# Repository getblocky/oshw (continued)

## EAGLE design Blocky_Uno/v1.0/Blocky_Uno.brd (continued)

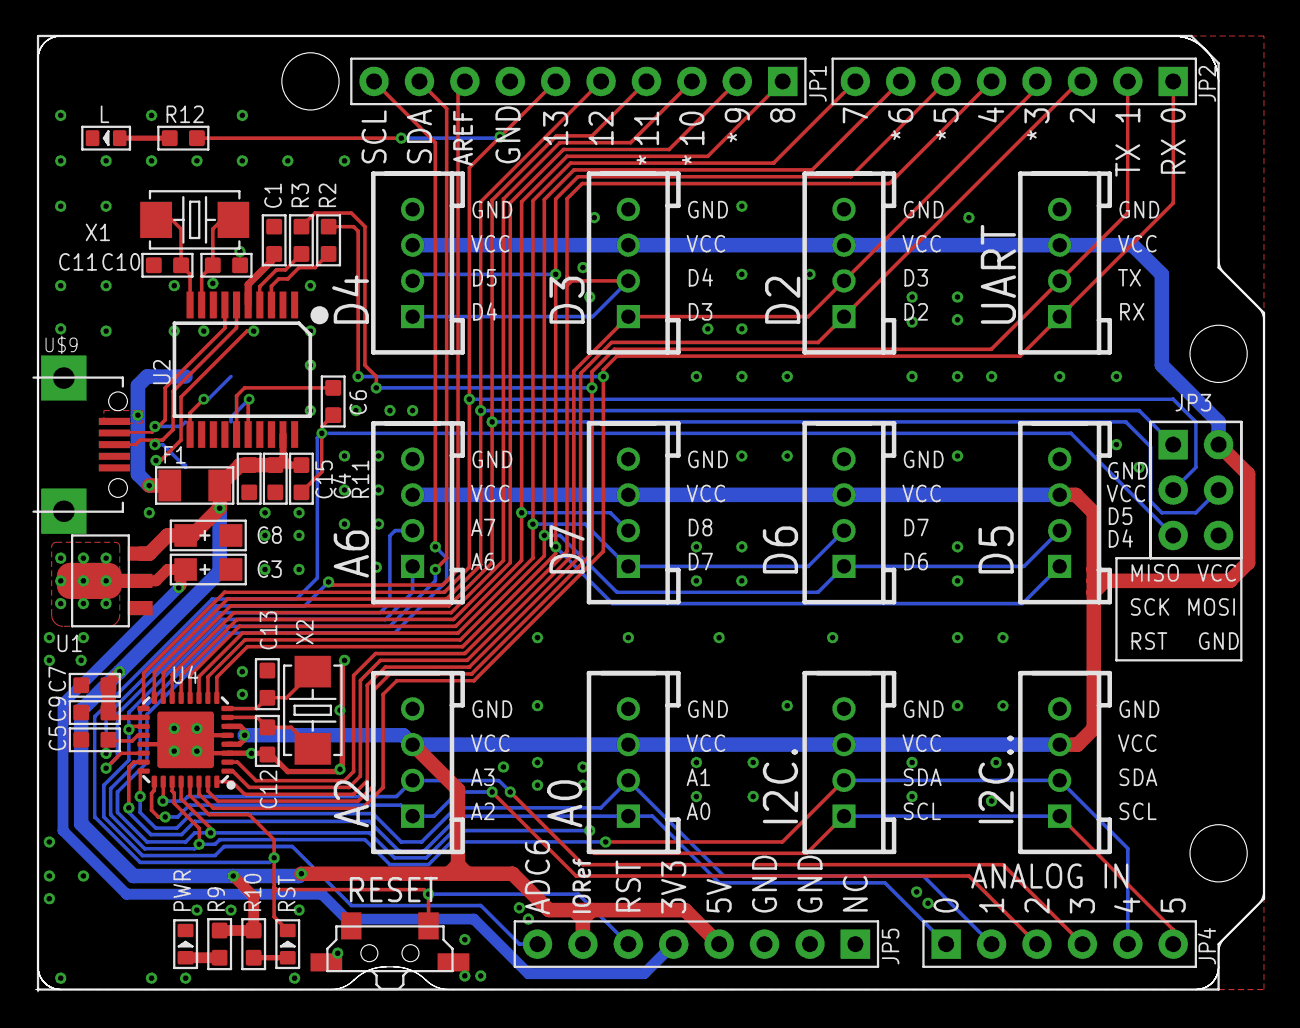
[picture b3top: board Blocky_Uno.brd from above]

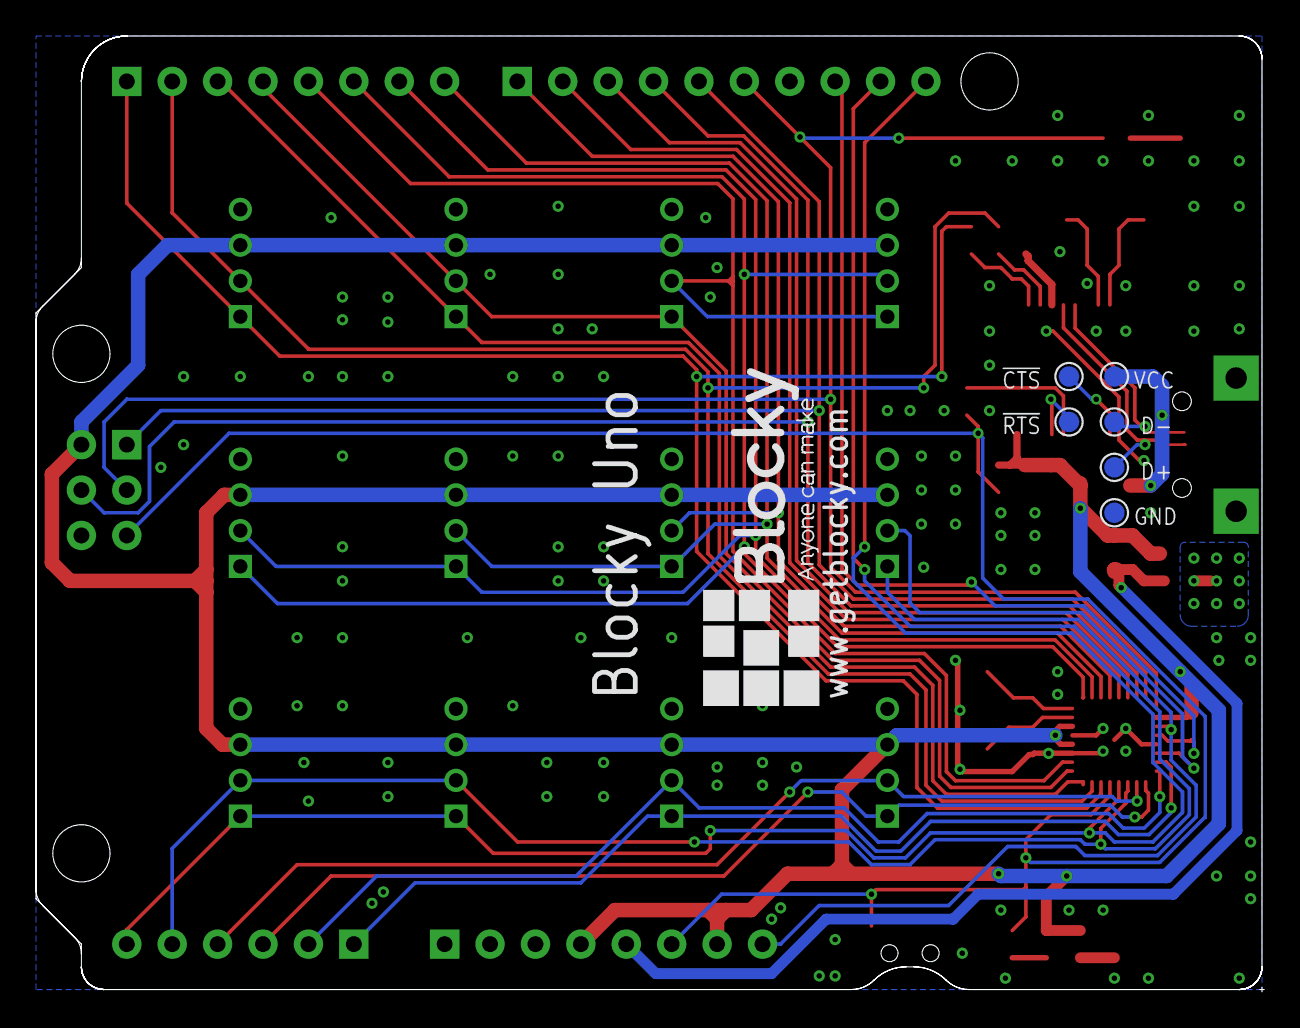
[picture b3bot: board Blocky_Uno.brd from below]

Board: 2 copper layers, 68.7 x 53.5 mm, 51 parts (7 on the bottom side), 43 nets.

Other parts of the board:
U$4: BLOCKY_LOGO
U$12: SEEED_MASK

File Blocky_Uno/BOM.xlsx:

| Part | Package | Quantity | Link
 | DIP Grove | 4P-2.0 | 12
 | 10nF | C0603 | 1
 | Cap tantalum 3216 22uF 10V | AVX-A 3216 | 2 | https://www.aliexpress.com/item/Free-shipping-20pcs-A-3216-2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
 | 100nF | C0603 | 6
 | 12pF | C0603 | 4
 | Fuse 1206 500mA | F1206 | 1 | https://www.aliexpress.com/item/100PCS-1206-0-5A-0-5-Amp-500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
 | MICRO-B-SMD 10118193-0001LF | MICRO-USB | 1 | https://www.digikey.com/product-detail/en/amphenol-fci/10118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
 | LED GREEN | LED-0603 | 2
 | Resistor 1k | R0603 | 5
 | Resistor 10k | R0603 | 1
 | Side SMD Tact Switch 3.5x7.0x3.5 TS-118E | 4P-SMD-7X3.5X3.5H | 1 | https://www.aliexpress.com/item/1000pcs-on-tape-reel-Horizon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
 | LED RED | LED-0603 | 1
 | LDO AMS1117-3.3V SOT89 | SOT89 | 1 | https://www.aliexpress.com/item/100PCS-AMS1117-3-3V-AMS1117-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
 | CH340T | SSOP20 | 1 | https://www.aliexpress.com/item/Smd-CH340T-wch-usb-to-serial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
 | Atmega328p-mu | MLF32X-W/HEAT | 1 | https://www.aliexpress.com/item/Free-Shipping-ATMEGA328P-MUR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
 | Crystal SMD 5032 12MHz | 2P-SMD-5X3.2 | 1 | https://www.aliexpress.com/item/NDK-NX5032GA-NX5032GB-12M-12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
 | Crystal SMD 5032 16MHz | 2P-SMD-5X3.2 | 1 | Crystal SMD 16MHz 5032 https://www.aliexpress.com/item/20PCS-16MHZ-5032-SMD-Pas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

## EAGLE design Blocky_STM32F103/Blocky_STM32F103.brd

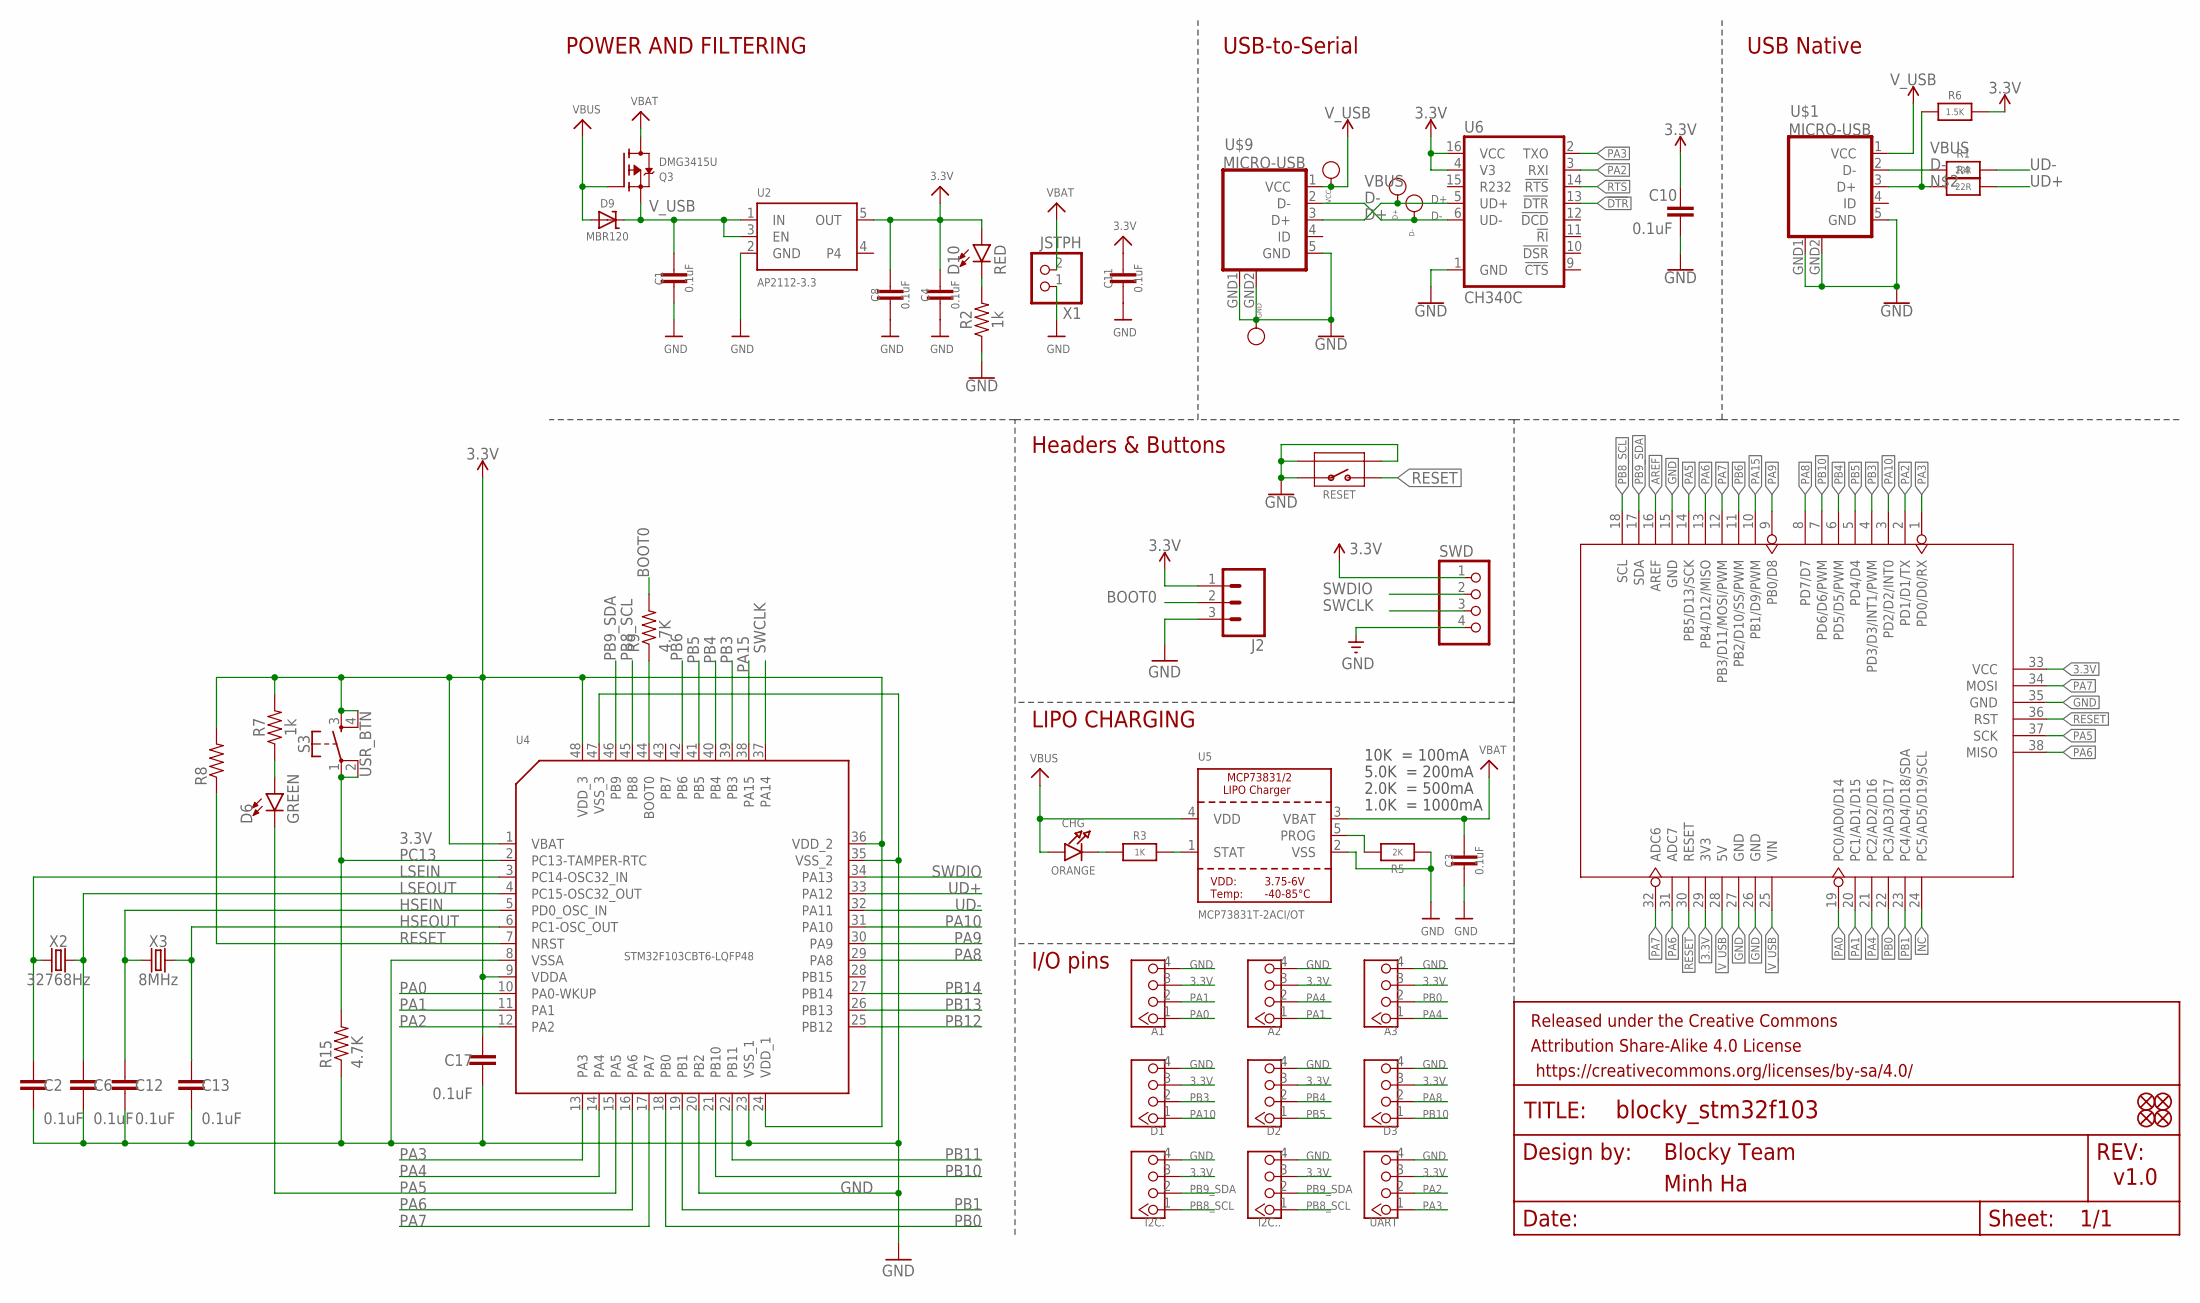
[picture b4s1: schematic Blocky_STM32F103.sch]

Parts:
A1, A2, A3: TWIG-4P-2.0-2.0; 4P-2.0
C1, C2, C3, C4, C6, C8, C10, C11, C12, C13, C17: 0.1uF; 0603
CHG: ORANGE; CHIPLED_0603
D1, D2, D3: TWIG-4P-2.0-2.0; 4P-2.0
D6: GREEN; LED-0603
D9: MBR120; SOD-123
D10: RED; LED-0603
D+: PAD-TEST-POINT'4545'; TP_4545
D-: PAD-TEST-POINT'4545'; TP_4545
FD1, FD2, FD3, FD4: FIDUCIAL1X2; FIDUCIAL-1X2
FRAME1: FRAME-LETTERNO_PACKAGE; DUMMY
GND: PAD-TEST-POINT'4545'; TP_4545
I2C., I2C..: TWIG-4P-2.0-2.0; 4P-2.0
J2: CONN_031X03_NO_SILK; 1X03_NO_SILK
Q3: DMG3415U; SOT23-R
R1, R4: 22R; 0603-NO
R2, R7: 1k; 0603
R3: 1K; 0603-NO
R5: 2K; 0603-NO
R6: 1.5K; 0603-NO
R8: 0603
R9, R15: 4.7K; 0603
RESET: BUTTON-4P-REINFORCE'TS-1188E'; 4P-SMD-7X3.5X3.5H
S3: USR_BTN; TACTILE_SWITCH_SMD_4.6X2.8MM
SWD: HEADER-1X4ROUND; 1X04_ROUND
U2: AP2112-3.3; SOT23-5
U3: ARDUINO-38P
U4: STM32F103CBT6-LQFP48; LQFP48-0.5-7X7MM
U5: MCP73831T-2ACI/OT; SOT23-5
U6: CH340C; SO016
U$1, U$9: MICRO-USB
UART: TWIG-4P-2.0-2.0; 4P-2.0
VCC: PAD-TEST-POINT'4545'; TP_4545
X1: JSTPH; JSTPH2
X2: 32768Hz; CRYSTAL-SMD-3.2X1.5MM
X3: 8MHz; CRYSTAL-SMD-5X3.2-2PAD

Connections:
3.3V: A1.3, A2.3, A3.3, C4.1, C8.1, C10.1, C11.1, C17.1, D1.3, D2.3, D3.3, D10.A, I2C..3, I2C...3, J2.1, R6.2, R7.2, R8.2, S3.3, S3.4, SWD.1, U2.5 (OUT), U3.29 (3V3), U3.33 (VCC), U4.1 (VBAT), U4.9 (VDDA), U4.24 (VDD_1), U4.36 (VDD_2), U4.48 (VDD_3), U6.4 (V3), U6.16 (VCC), UART.3
!DTR: U6.13 (!DTR)
!RTS: U6.14 (!RTS)
AREF: U3.16 (AREF)
BOOT0: J2.2, R9.2
D+: D+.T, U6.5 (UD+), U$9.3 (D+)
D-: D-.T, R1.1, U6.6 (UD-), U$1.2 (D-), U$9.2 (D-)
GND: A1.4, A2.4, A3.4, C1.2, C2.2, C3.2, C4.2, C6.2, C8.2, C10.2, C11.2, C12.2, C13.2, C17.2, D1.4, D2.4, D3.4, GND.T, I2C..4, I2C...4, J2.3, R2.1, R5.1, R15.1, RESET.1, RESET.S1, RESET.S2, SWD.4, U2.2 (GND), U3.15 (GND), U3.26 (GND), U3.27 (GND), U3.35 (GND), U4.8 (VSSA), U4.20 (PB2), U4.23 (VSS_1), U4.35 (VSS_2), U4.47 (VSS_3), U5.2 (VSS), U6.1 (GND), U$1.5 (GND), U$1.GND1 (GND), U$1.GND2 (GND), U$9.5 (GND), U$9.GND1 (GND), U$9.GND2 (GND), UART.4, X1.1
HSEIN: C12.1, U4.5 (PD0_OSC_IN), X3.P$1 (1)
HSEOUT: C13.1, U4.6 (PC1-OSC_OUT), X3.P$2 (2)
LSEIN: C2.1, U4.3 (PC14-OSC32_IN), X2.P$1 (1)
LSEOUT: C6.1, U4.4 (PC15-OSC32_OUT), X2.P$2 (2)
unnamed: CHG.C, R3.1
unnamed: R4.1, R6.1, U$1.3 (D+)
unnamed: R9.1, U4.44 (BOOT0)
unnamed: D10.C, R2.2
unnamed: D6.A, R7.1
NC: U3.24 (PC5/AD5/D19/SCL)
PA0: A1.1, U3.19 (PC0/AD0/D14), U4.10 (PA0-WKUP)
PA1: A1.2, A2.1, U3.20 (PC1/AD1/D15), U4.11 (PA1)
PA2: U3.2 (PD1/D1/TX), U4.12 (PA2), U6.3 (RXI), UART.2
PA3: U3.1 (PD0/D0/RX), U4.13 (PA3), U6.2 (TXO), UART.1
PA4: A2.2, A3.1, U3.21 (PC2/AD2/D16), U4.14 (PA4)
PA5: D6.C, U3.14 (PB5/D13/SCK), U3.37 (SCK), U4.15 (PA5)
PA6: U3.13 (PB4/D12/MISO), U3.31 (ADC7), U3.38 (MISO), U4.16 (PA6)
PA7: U3.12 (PB3/D11/MOSI/PWM), U3.32 (ADC6), U3.34 (MOSI), U4.17 (PA7)
PA8: D3.2, U3.8 (PD7/D7), U4.29 (PA8)
PA9: U3.9 (PB0/D8), U4.30 (PA9)
PA10: D1.1, U3.3 (PD2/D2/INT0), U4.31 (PA10)
PA15: U3.10 (PB1/D9/PWM), U4.38 (PA15)
PB0: A3.2, U3.22 (PC3/AD3/D17), U4.18 (PB0)
PB1: U3.23 (PC4/AD4/D18/SDA), U4.19 (PB1)
PB3: D1.2, U3.4 (PD3/D3/INT1/PWM), U4.39 (PB3)
PB4: D2.2, U3.6 (PD5/D5/PWM), U4.40 (PB4)
PB5: D2.1, U3.5 (PD4/D4), U4.41 (PB5)
PB6: U3.11 (PB2/D10/SS/PWM), U4.42 (PB6)
PB8_SCL: I2C..1, I2C...1, U3.18 (SCL), U4.45 (PB8)
PB9_SDA: I2C..2, I2C...2, U3.17 (SDA), U4.46 (PB9)
PB10: D3.1, U3.7 (PD6/D6/PWM), U4.21 (PB10)
PB11: U4.22 (PB11)
PB12: U4.25 (PB12)
PB13: U4.26 (PB13)
PB14: U4.27 (PB14)
PC13: R15.2, S3.1, S3.2, U4.2 (PC13-TAMPER-RTC)
PROG: R5.2, U5.5 (PROG)
RESET: R8.1, RESET.2, U3.30 (RESET), U3.36 (RST), U4.7 (NRST)
STAT: R3.2, U5.1 (STAT)
SWCLK: SWD.3, U4.37 (PA14)
SWDIO: SWD.2, U4.34 (PA13)
UD+: R4.2, U4.33 (PA12)
UD-: R1.2, U4.32 (PA11)
VBAT: C3.1, Q3.3 (D), U5.3 (VBAT), X1.2
VBUS: CHG.A, D9.A, Q3.1 (G), U5.4 (VDD), U$1.1 (VCC), U$9.1 (VCC), VCC.T
V_USB: C1.1, D9.C, Q3.2 (S), U2.1 (IN), U2.3 (EN), U3.25 (VIN), U3.28 (5V)

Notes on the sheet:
POWER AND FILTERING
USB-to-Serial
I/O pins
Headers & Buttons
USB Native
LIPO CHARGING
Blocky Team
v1.0
Minh Ha
10K = 100mA
5.0K = 200mA
2.0K = 500mA
1.0K = 1000mA

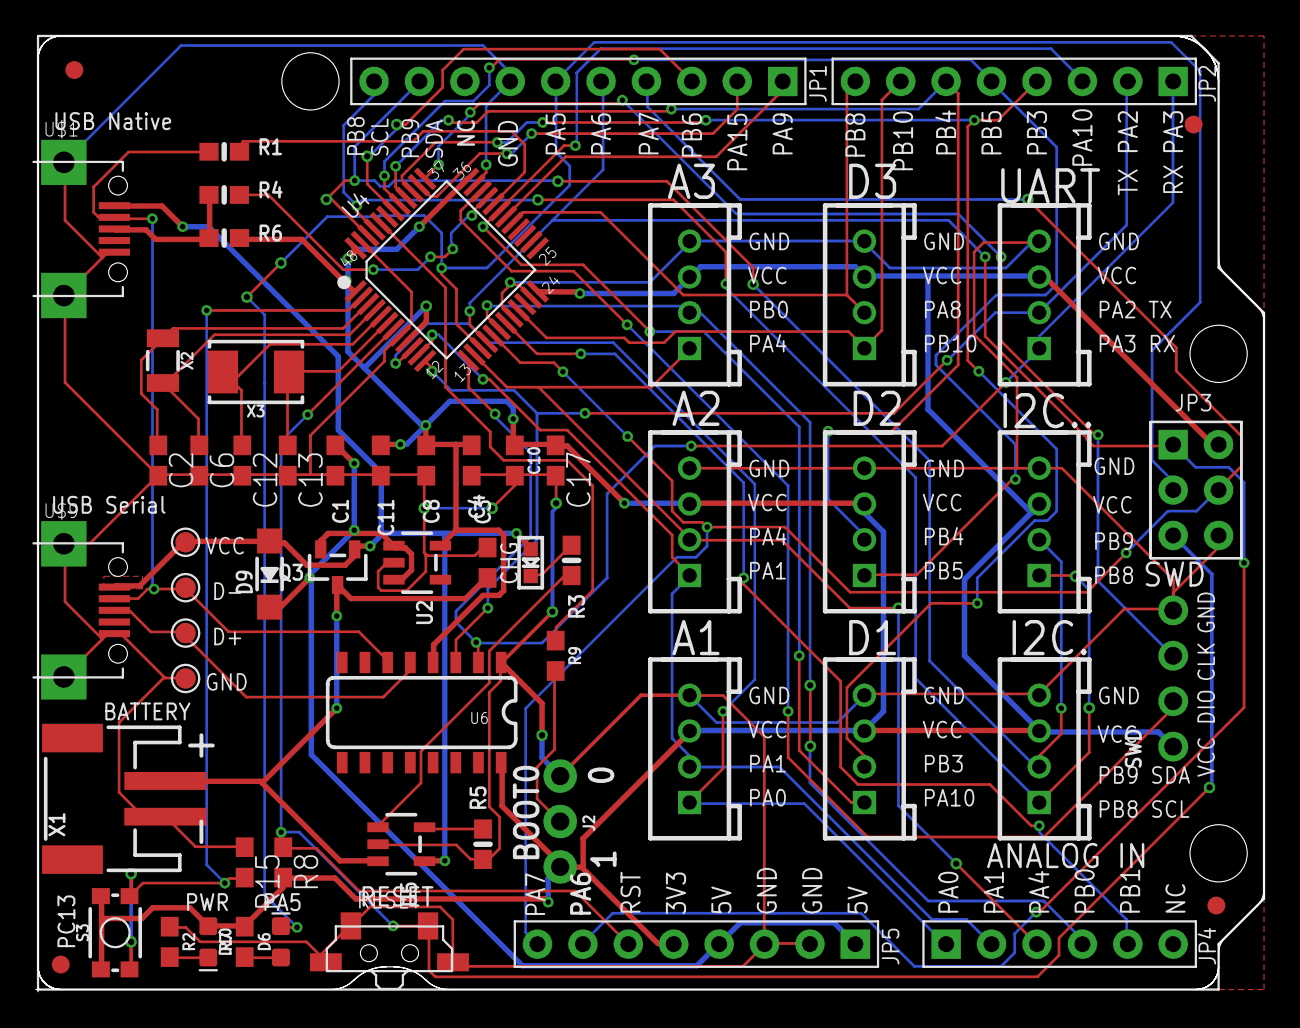
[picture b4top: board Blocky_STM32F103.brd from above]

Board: 2 copper layers, 68.7 x 53.5 mm, 59 parts (1 on the bottom side), 46 nets.

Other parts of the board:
U$4: BLOCKY_LOGO

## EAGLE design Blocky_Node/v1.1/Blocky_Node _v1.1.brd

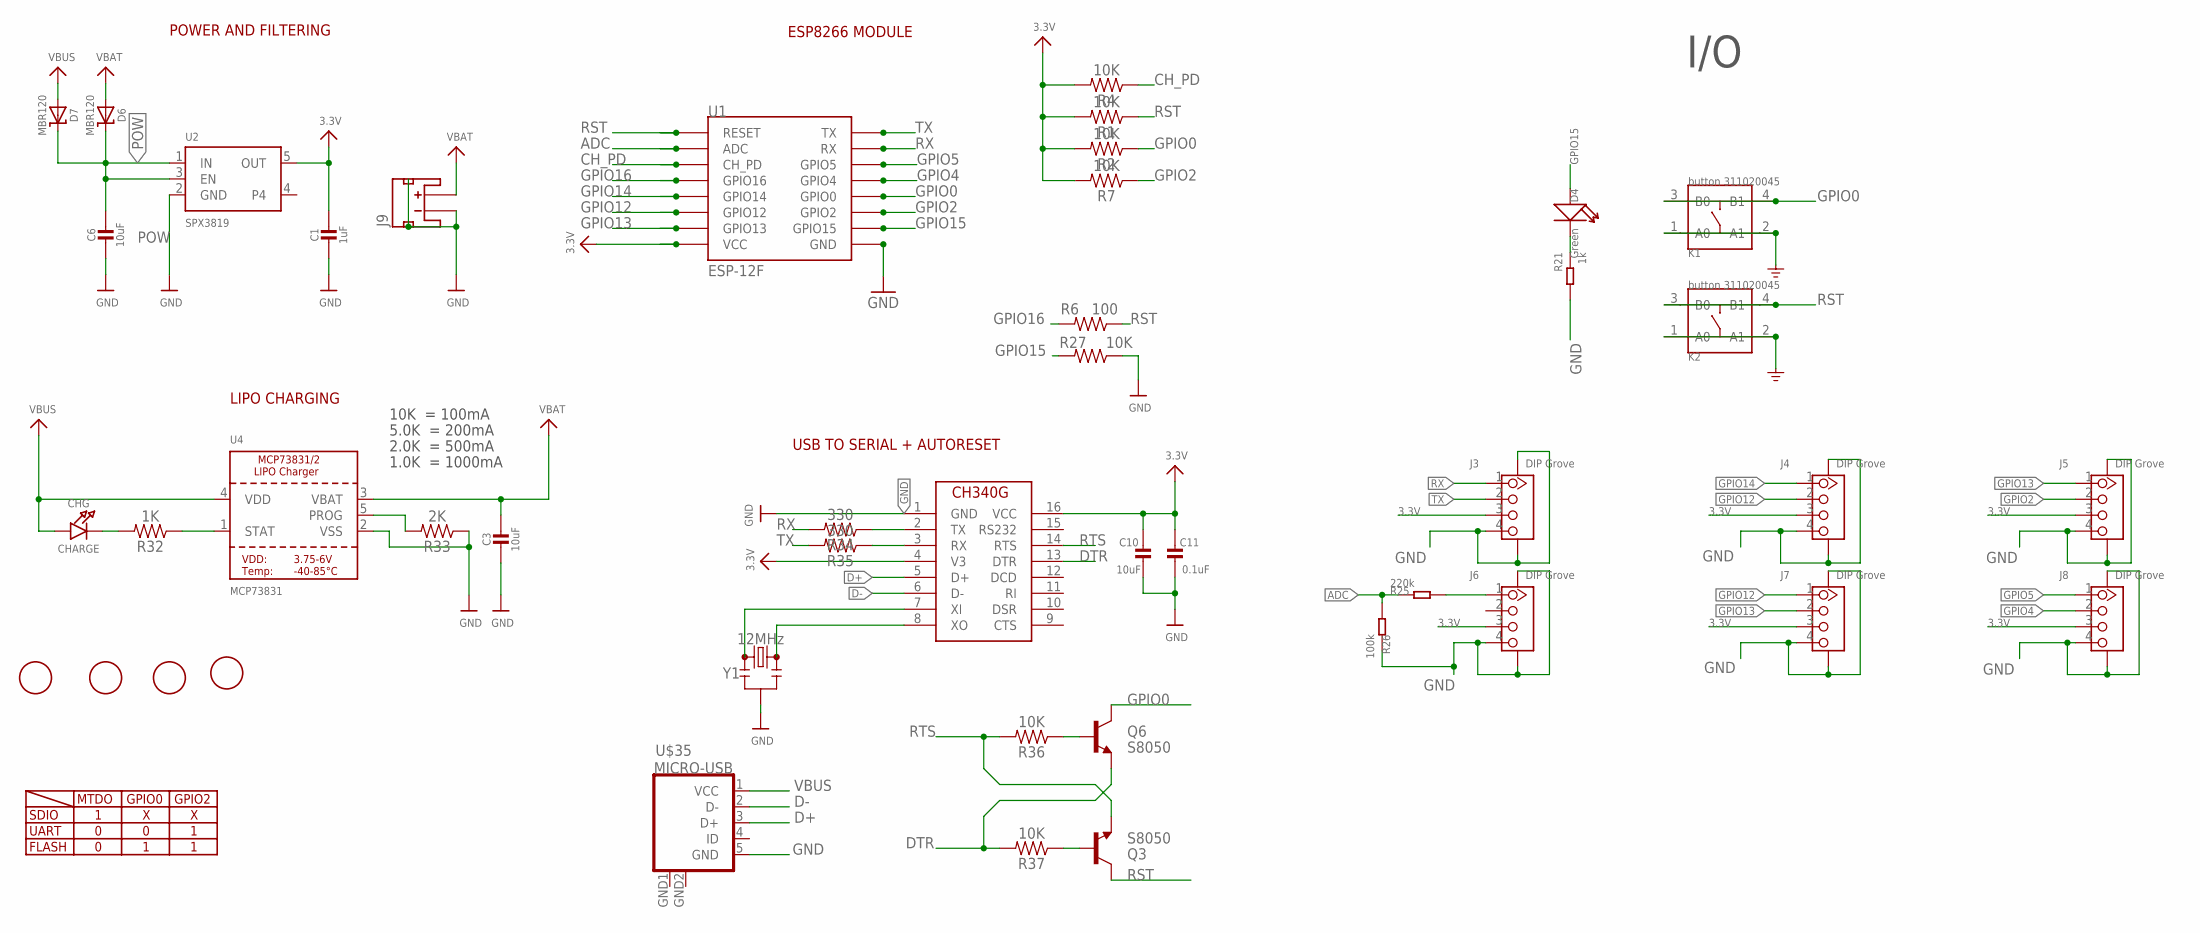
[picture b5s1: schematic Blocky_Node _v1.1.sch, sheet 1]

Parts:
C1: 1uF; _0603
C3, C6, C10: 10uF; _0603
C11: 0.1uF; _0603
CHG: CHARGE; CHIPLED_0603
D4: Green; LED-0603
D6, D7: MBR120; SOD-123
J3, J4, J5, J6, J7, J8: DIP Grove; HW4-SMD-2.0-90D
J9: JST_2MM_MALE; JST-2-SMD
K1, K2: button 311020045; SW4P-SMD-4.5X3.2X2.5MM
Q3, Q6: S8050; SOT23-3
R1, R2, R4, R7, R27, R36, R37: 10K; 0603
R6: 100; 0603
R21: 1k; R0603
R25: 220k; R0603
R26: 100k; R0603
R32: 1K; 0603
R33: 2K; 0603
R34, R35: 330; 0603
U1: ESP-12F; ESP12-SMD
U2: SPX3819; SOT23-5
U4: MCP73831; SOT23-5@1
U$9, U$10, U$11, U$12: FIDUCIAL; FIDUCIAL_1MM
U$35: MICRO-USB
U$44: CH340G; SOIC16
Y1: 12MHz; RESONATOR-SMD-3.2X1.3

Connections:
3.3V: C1.1, C10.1, C11.1, J3.3, J4.3, J5.3, J6.3, J7.3, J8.3, R1.2, R2.2, R4.2, R7.2, U1.VCC, U2.5 (OUT), U$44.4 (V3), U$44.16 (VCC)
ADC: R25.1, R26.2, U1.ADC
CH_PD: R4.1, U1.CH_PD
D+: U$35.3 (D+), U$44.5 (D+)
D-: U$35.2 (D-), U$44.6 (D-)
DTR: Q6.2 (E), R37.2, U$44.13 (DTR)
GND: C1.2, C3.2, C6.2, C10.2, C11.2, J3.4, J3.SS1, J3.SS2, J4.4, J4.SS1, J4.SS2, J5.4, J5.SS1, J5.SS2, J6.4, J6.SS1, J6.SS2, J7.4, J7.SS1, J7.SS2, J8.4, J8.SS1, J8.SS2, J9.1 (-), J9.NC1 (PAD1), J9.NC2 (PAD2), K1.1 (A0), K1.2 (A1), K2.1 (A0), K2.2 (A1), R21.2, R26.1, R27.1, R33.1, U1.GND, U2.2 (GND), U4.2 (VSS), U$35.5 (GND), U$35.GND1 (GND), U$35.GND2 (GND), U$44.1 (GND), Y1.2
GPIO0: K1.3 (B0), K1.4 (B1), Q6.3 (C), R2.1, U1.GPIO0
GPIO2: J5.2, R7.1, U1.GPIO2
GPIO4: J8.2, U1.GPIO4
GPIO5: J8.1, U1.GPIO5
GPIO12: J4.2, J7.1, U1.GPIO12
GPIO13: J5.1, J7.2, U1.GPIO13
GPIO14: J4.1, U1.GPIO14
GPIO15: D4.+, R27.2, U1.GPIO15
GPIO16: R6.2, U1.GPIO16
unnamed: CHG.C, R32.2
unnamed: Q3.1 (B), R37.1
unnamed: Q6.1 (B), R36.1
unnamed: U$44.7 (XI), Y1.1
unnamed: J6.1, R25.2
unnamed: U$44.8 (XO), Y1.3
unnamed: D4.-, R21.1
unnamed: R34.1, U$44.2 (TX)
unnamed: R35.1, U$44.3 (RX)
POW: C6.1, D6.C, D7.C, U2.1 (IN), U2.3 (EN)
PROG: R33.2, U4.5 (PROG)
RST: K2.3 (B0), K2.4 (B1), Q3.3 (C), R1.1, R6.1, U1.RESET
RTS: Q3.2 (E), R36.2, U$44.14 (RTS)
RX: J3.1, R34.2, U1.RXD0 (RX)
STAT: R32.1, U4.1 (STAT)
TX: J3.2, R35.2, U1.TXD0 (TX)
VBAT: C3.1, D6.A, J9.2 (+), U4.3 (VBAT)
VBUS: CHG.A, D7.A, U4.4 (VDD), U$35.1 (VCC)

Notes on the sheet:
SDIO
UART
FLASH
MTDO
GPIO0
GPIO2
POWER AND FILTERING
ESP8266 MODULE
10K = 100mA
5.0K = 200mA
2.0K = 500mA
1.0K = 1000mA
LIPO CHARGING
USB TO SERIAL + AUTORESET
I/O

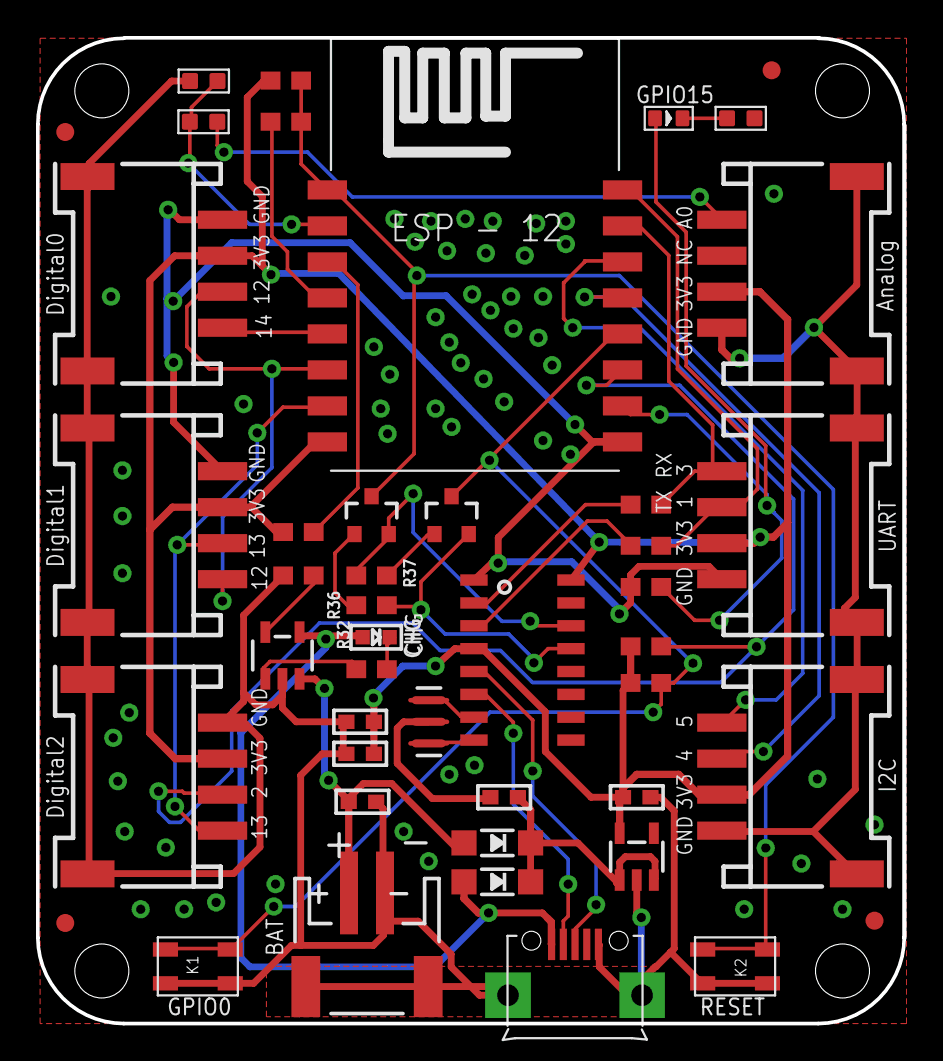
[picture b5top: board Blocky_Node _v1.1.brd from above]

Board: 2 copper layers, 48.2 x 54.8 mm, 46 parts (1 on the bottom side), 34 nets.

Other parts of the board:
U$15: BLOCKY_LOGO

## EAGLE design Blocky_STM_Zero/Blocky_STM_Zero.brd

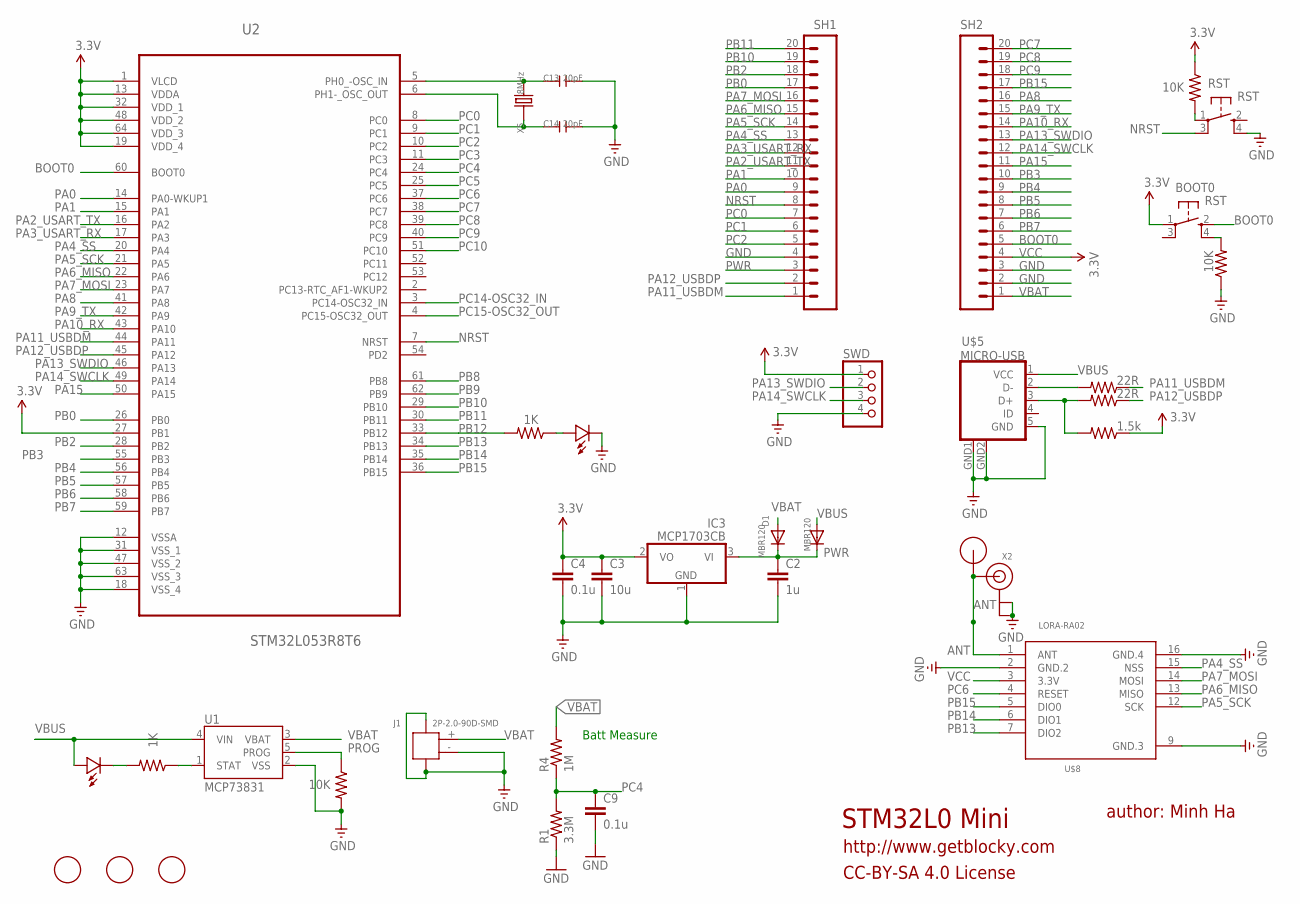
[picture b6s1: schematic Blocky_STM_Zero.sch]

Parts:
BOOT0: RST; KMR2
C2: 1u; 0603-CAP
C3: 10u; 0603-CAP
C4, C9: 0.1u; 0603-CAP
C13, C14: 20pF; C0603
CHGR: RED; 0603-LED
D1: MBR120; SOD-123
IC3: MCP1703CB; SOT23
J1: 2P-2.0-90D-SMD; HW2-SMD-2.0-90D
MBR0001: MBR120; SOD-123
R1: 3.3M; R0603
R2, R5: 1K; 0603-RES
R3, R7: 22R; 0603-RES
R4: 1M; R0603
R6, R9, R10: 10K; 0603-RES
R8: 1.5k; 0603-RES
RST: RST; KMR2
SH1, SH2: M20; 1X20
SWD: HEADER-1X4ROUND; 1X04_ROUND
U1: MCP73831; SOT23-5
U2: STM32L053R8T6; QFP50P1200X1200X160-64N
U$1: RFM12B_ANTENNA; RFM12B-ANTENNA
U$2, U$4, U$7: FIDUCIAL; FIDUCIAL_1MM
U$5: MICRO-USB
U$6: LED0603; 0603-LED
U$8: LORA-RA02; LORA-RA2-SMD
X2: ANTENNA_U.FL; U.FL
X5: 8MHz; 2P-SMD-5X3.2

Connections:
ANT: U$1.P$1, U$8.1 (ANT), X2.3 (SIGNAL)
BOOT0: BOOT0.2 (S), SH2.5, U2.60 (BOOT0)
GND: C2.2, C3.2, C4.2, C9.2, C13.2, C14.2, IC3.1 (GND), J1.3, J1.4, J1.- (2), R1.1, R6.2, R9.1, RST.4 (S1), SH1.4, SH2.2, SH2.3, SWD.4, U1.2 (VSS), U2.12 (VSSA), U2.18 (VSS_4), U2.31 (VSS_1), U2.47 (VSS_2), U2.63 (VSS_3), U$5.5 (GND), U$5.GND1 (GND), U$5.GND2 (GND), U$6.MINUS, U$8.2 (GND.2), U$8.9 (GND.3), U$8.16 (GND.4), X2.1 (GND), X2.2 (GND)
unnamed: BOOT0.4 (S1), R9.2
unnamed: R2.1, U$6.PLUS
unnamed: CHGR.MINUS, R5.2
NRST: RST.3 (P1), SH1.8, U2.7 (NRST)
OSC_IN: C13.1, U2.5 (PH0_-OSC_IN), X5.2
OSC_OUT: C14.1, U2.6 (PH1-_OSC_OUT), X5.1
PA0: SH1.9, U2.14 (PA0-WKUP1)
PA1: SH1.10, U2.15 (PA1)
PA2_USART_TX: SH1.11, U2.16 (PA2)
PA3_USART_RX: SH1.12, U2.17 (PA3)
PA4_SS: SH1.13, U2.20 (PA4), U$8.15 (NSS)
PA5_SCK: SH1.14, U2.21 (PA5), U$8.12 (SCK)
PA6_MISO: SH1.15, U2.22 (PA6), U$8.13 (MISO)
PA7_MOSI: SH1.16, U2.23 (PA7), U$8.14 (MOSI)
PA8: SH2.16, U2.41 (PA8)
PA9_TX: SH2.15, U2.42 (PA9)
PA10_RX: SH2.14, U2.43 (PA10)
PA11_USBDM: R3.1, SH1.1, U2.44 (PA11)
PA12_USBDP: R7.1, SH1.2, U2.45 (PA12)
PA13_SWDIO: SH2.13, SWD.2, U2.46 (PA13)
PA14_SWCLK: SH2.12, SWD.3, U2.49 (PA14)
PA15: SH2.11, U2.50 (PA15)
PB0: SH1.17, U2.26 (PB0)
PB2: SH1.18, U2.28 (PB2)
PB3: SH2.10, U2.55 (PB3)
PB4: SH2.9, U2.56 (PB4)
PB5: SH2.8, U2.57 (PB5)
PB6: SH2.7, U2.58 (PB6)
PB7: SH2.6, U2.59 (PB7)
PB8: U2.61 (PB8)
PB9: U2.62 (PB9)
PB10: SH1.19, U2.29 (PB10)
PB11: SH1.20, U2.30 (PB11)
PB12: R2.2, U2.33 (PB12)
PB13: U2.34 (PB13), U$8.7 (DIO2)
PB14: U2.35 (PB14), U$8.6 (DIO1)
PB15: SH2.17, U2.36 (PB15), U$8.5 (DIO0)
PC0: SH1.7, U2.8 (PC0)
PC1: SH1.6, U2.9 (PC1)
PC2: SH1.5, U2.10 (PC2)
PC3: U2.11 (PC3)
PC4: C9.1, R1.2, R4.1, U2.24 (PC4)
PC5: U2.25 (PC5)
PC6: U2.37 (PC6), U$8.4 (RESET)
PC7: SH2.20, U2.38 (PC7)
PC8: SH2.19, U2.39 (PC8)
PC9: SH2.18, U2.40 (PC9)
PC10: U2.51 (PC10)
PC14-OSC32_IN: U2.3 (PC14-OSC32_IN)
PC15-OSC32_OUT: U2.4 (PC15-OSC32_OUT)
PROG: R6.1, U1.5 (PROG)
PWR: C2.1, D1.C, IC3.3 (VI), MBR0001.C, SH1.3
RST_1: R10.2, RST.1
STAT: R5.1, U1.1 (STAT)
USB_D+: R7.2, R8.2, U$5.3 (D+)
USB_D-: R3.2, U$5.2 (D-)
VBAT: D1.A, J1.+ (1), R4.2, SH2.1, U1.3 (VBAT)
VBUS: CHGR.PLUS, MBR0001.A, U1.4 (VIN), U$5.1 (VCC)
VCC: BOOT0.1, C3.1, C4.1, IC3.2 (VO), R8.1, R10.1, SH2.4, SWD.1, U2.1 (VLCD), U2.13 (VDDA), U2.19 (VDD_4), U2.27 (PB1), U2.32 (VDD_1), U2.48 (VDD_2), U2.64 (VDD_3), U$8.3 (3.3V)

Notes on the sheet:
STM32L0 Mini
author: Minh Ha
http://www.getblocky.com
CC-BY-SA 4.0 License
Batt Measure

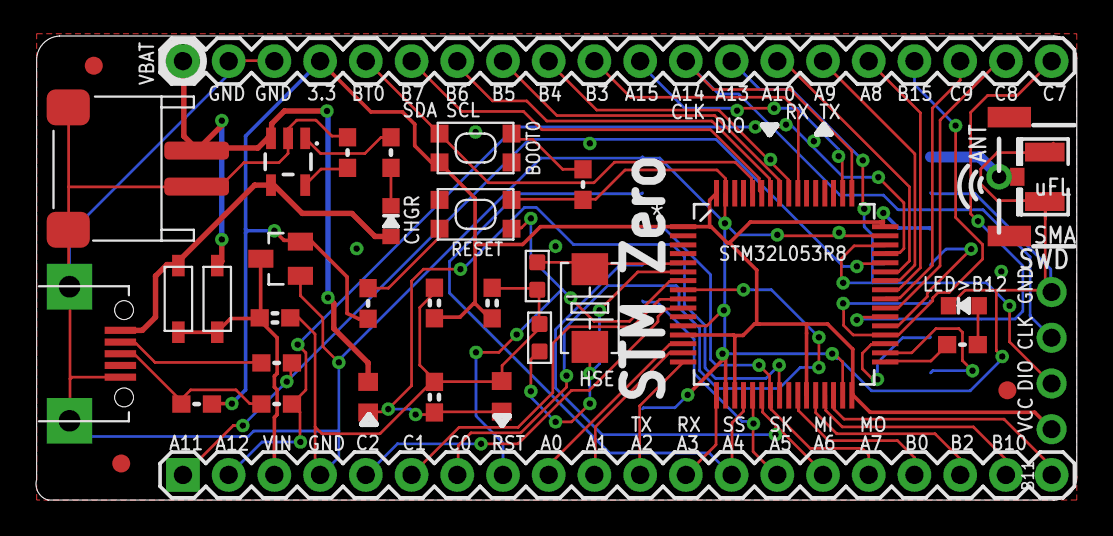
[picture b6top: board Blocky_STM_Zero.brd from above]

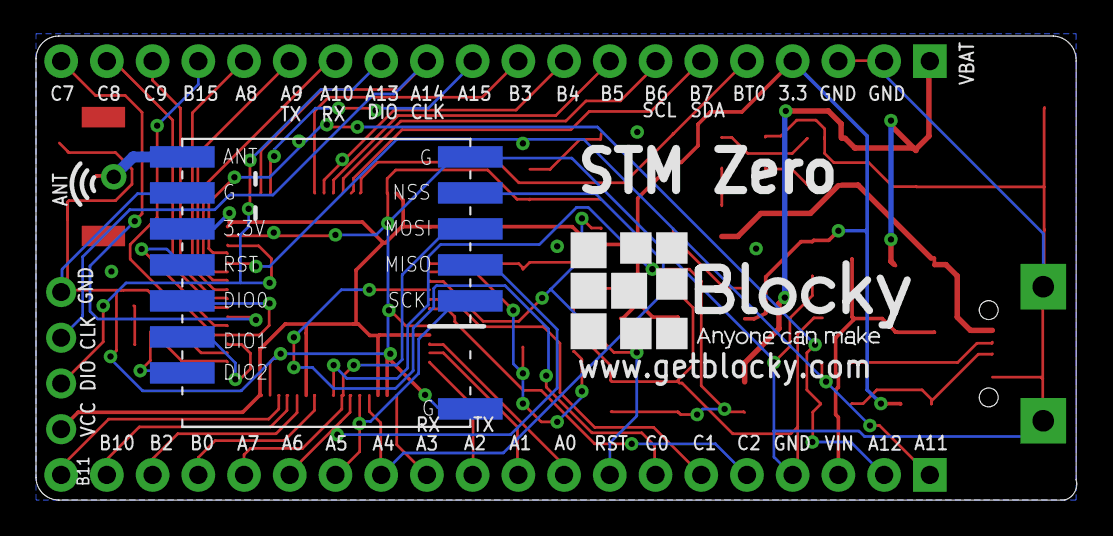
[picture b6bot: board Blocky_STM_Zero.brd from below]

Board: 2 copper layers, 57.8 x 25.8 mm, 38 parts (2 on the bottom side), 55 nets.

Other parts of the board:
U$3: BLOCKY_LOGO

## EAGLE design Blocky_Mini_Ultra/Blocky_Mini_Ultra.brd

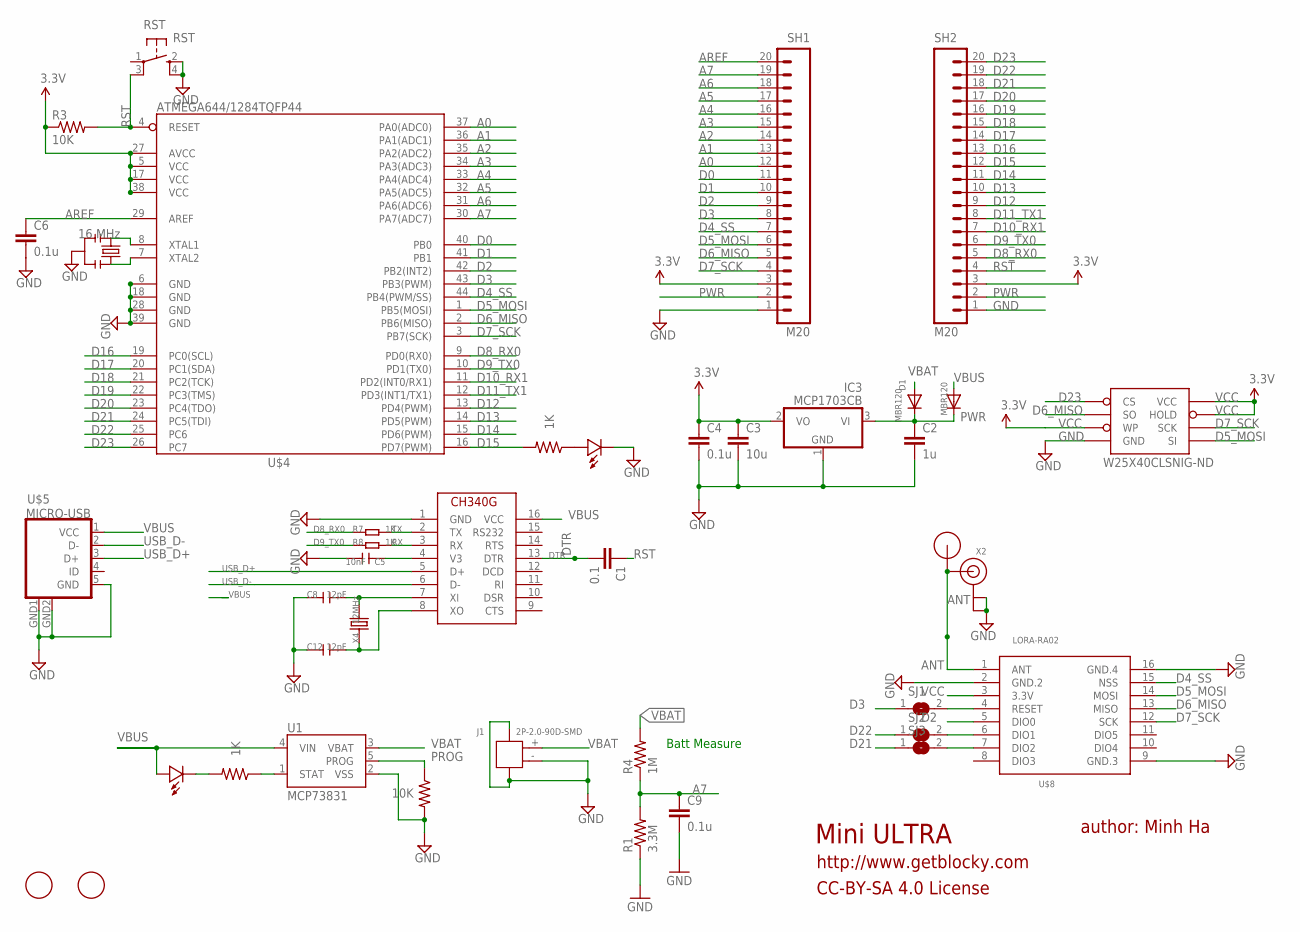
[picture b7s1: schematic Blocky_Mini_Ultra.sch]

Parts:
C1: 0.1; 0603-CAP
C2: 1u; 0603-CAP
C3: 10u; 0603-CAP
C4, C6, C9: 0.1u; 0603-CAP
C5: 10nF; C0603
C8, C12: 12pF; C0603
CHG: RED; 0603-LED
D1: MBR120; SOD-123
IC3: MCP1703CB; SOT23
J1: 2P-2.0-90D-SMD; HW2-SMD-2.0-90D
MBR0001: MBR120; SOD-123
R1: 3.3M; R0603
R2, R5: 1K; 0603-RES
R3, R6: 10K; 0603-RES
R4: 1M; R0603
R7, R8: 1K; R0603
RST: RST; KMR2
SH1, SH2: M20; 1X20
SJ1, SJ2, SJ3: SOLDERJUMPER; SOLDERJUMPER_ARROW_NOPASTE
U1: MCP73831; SOT23-5
U$1: RFM12B_ANTENNA; RFM12B-ANTENNA
U$2, U$7: FIDUCIAL; FIDUCIAL_1MM
U$4: ATMEGA644/1284TQFP44; TQFP44
U$5: MICRO-USB
U$6: LED0603; 0603-LED
U$8: LORA-RA02; LORA-RA2-SMD
U$9: CH340G; SOIC16
W25X40CLSNIG-ND: AT25F512BWIDE_5.3MM; SO08WIDE
X1: 16 MHz; RESONATOR-SMD
X2: ANTENNA_U.FL; U.FL
X4: 12MHz; 2P-SMD-5X3.2

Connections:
A0: SH1.12, U$4.37 (PA0(ADC0))
A1: SH1.13, U$4.36 (PA1(ADC1))
A2: SH1.14, U$4.35 (PA2(ADC2))
A3: SH1.15, U$4.34 (PA3(ADC3))
A4: SH1.16, U$4.33 (PA4(ADC4))
A5: SH1.17, U$4.32 (PA5(ADC5))
A6: SH1.18, U$4.31 (PA6(ADC6))
A7: C9.1, R1.2, R4.1, SH1.19, U$4.30 (PA7(ADC7))
ANT: U$1.P$1, U$8.1 (ANT), X2.3 (SIGNAL)
AREF: C6.1, SH1.20, U$4.29 (AREF)
D0: SH1.11, U$4.40 (PB0)
D1: SH1.10, U$4.41 (PB1)
D2: SH1.9, U$4.42 (PB2(INT2)), U$8.5 (DIO0)
D3: SH1.8, SJ1.1, U$4.43 (PB3(PWM))
D4_SS: SH1.7, U$4.44 (PB4(PWM/SS)), U$8.15 (NSS)
D5_MOSI: SH1.6, U$4.1 (PB5(MOSI)), U$8.14 (MOSI), W25X40CLSNIG-ND.5 (SI)
D6_MISO: SH1.5, U$4.2 (PB6(MISO)), U$8.13 (MISO), W25X40CLSNIG-ND.2 (SO)
D7_SCK: SH1.4, U$4.3 (PB7(SCK)), U$8.12 (SCK), W25X40CLSNIG-ND.6 (SCK)
D8_RX0: R7.1, SH2.5, U$4.9 (PD0(RX0))
D9_TX0: R8.1, SH2.6, U$4.10 (PD1(TX0))
D10_RX1: SH2.7, U$4.11 (PD2(INT0/RX1))
D11_TX1: SH2.8, U$4.12 (PD3(INT1/TX1))
D12: SH2.9, U$4.13 (PD4(PWM))
D13: SH2.10, U$4.14 (PD5(PWM))
D14: SH2.11, U$4.15 (PD6(PWM))
D15: R2.2, SH2.12, U$4.16 (PD7(PWM))
D16: SH2.13, U$4.19 (PC0(SCL))
D17: SH2.14, U$4.20 (PC1(SDA))
D18: SH2.15, U$4.21 (PC2(TCK))
D19: SH2.16, U$4.22 (PC3(TMS))
D20: SH2.17, U$4.23 (PC4(TDO))
D21: SH2.18, SJ3.1, U$4.24 (PC5(TDI))
D22: SH2.19, SJ2.1, U$4.25 (PC6)
D23: SH2.20, U$4.26 (PC7), W25X40CLSNIG-ND.1 (CS)
DIO1: SJ2.2, U$8.6 (DIO1)
DIO2: SJ3.2, U$8.7 (DIO2)
DTR: C1.2, U$9.13 (DTR)
GND: C2.2, C3.2, C4.2, C5.2, C6.2, C8.1, C9.2, C12.1, IC3.1 (GND), J1.3, J1.4, J1.- (2), R1.1, R6.2, RST.2 (S), RST.4 (S1), SH1.1, SH2.1, U1.2 (VSS), U$4.6 (GND), U$4.18 (GND), U$4.28 (GND), U$4.39 (GND), U$5.5 (GND), U$5.GND1 (GND), U$5.GND2 (GND), U$6.MINUS, U$8.2 (GND.2), U$8.9 (GND.3), U$8.16 (GND.4), U$9.1 (GND), W25X40CLSNIG-ND.4 (GND), X1.2, X2.1 (GND), X2.2 (GND)
unnamed: U$4.8 (XTAL1), X1.1
unnamed: R2.1, U$6.PLUS
unnamed: U$4.7 (XTAL2), X1.3
unnamed: CHG.MINUS, R5.2
PROG: R6.1, U1.5 (PROG)
PWR: C2.1, D1.C, IC3.3 (VI), MBR0001.C, SH1.2, SH2.2
RA02_RST: SJ1.2, U$8.4 (RESET)
RST: C1.1, R3.2, RST.3 (P1), SH2.4, U$4.4 (RESET)
RX: R8.2, U$9.3 (RX)
STAT: R5.1, U1.1 (STAT)
TX: R7.2, U$9.2 (TX)
USB_D+: U$5.3 (D+), U$9.5 (D+)
USB_D-: U$5.2 (D-), U$9.6 (D-)
V3: C5.1, U$9.4 (V3)
VBAT: D1.A, J1.+ (1), R4.2, U1.3 (VBAT)
VBUS: CHG.PLUS, MBR0001.A, U1.4 (VIN), U$5.1 (VCC), U$9.16 (VCC)
VCC: C3.1, C4.1, IC3.2 (VO), R3.1, SH1.3, SH2.3, U$4.5 (VCC), U$4.17 (VCC), U$4.27 (AVCC), U$4.38 (VCC), U$8.3 (3.3V), W25X40CLSNIG-ND.3 (WP), W25X40CLSNIG-ND.7 (HOLD), W25X40CLSNIG-ND.8 (VCC)
XI: C8.2, U$9.7 (XI), X4.2
XO: C12.2, U$9.8 (XO), X4.1

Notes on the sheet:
Mini ULTRA
author: Minh Ha
http://www.getblocky.com
CC-BY-SA 4.0 License
Batt Measure
